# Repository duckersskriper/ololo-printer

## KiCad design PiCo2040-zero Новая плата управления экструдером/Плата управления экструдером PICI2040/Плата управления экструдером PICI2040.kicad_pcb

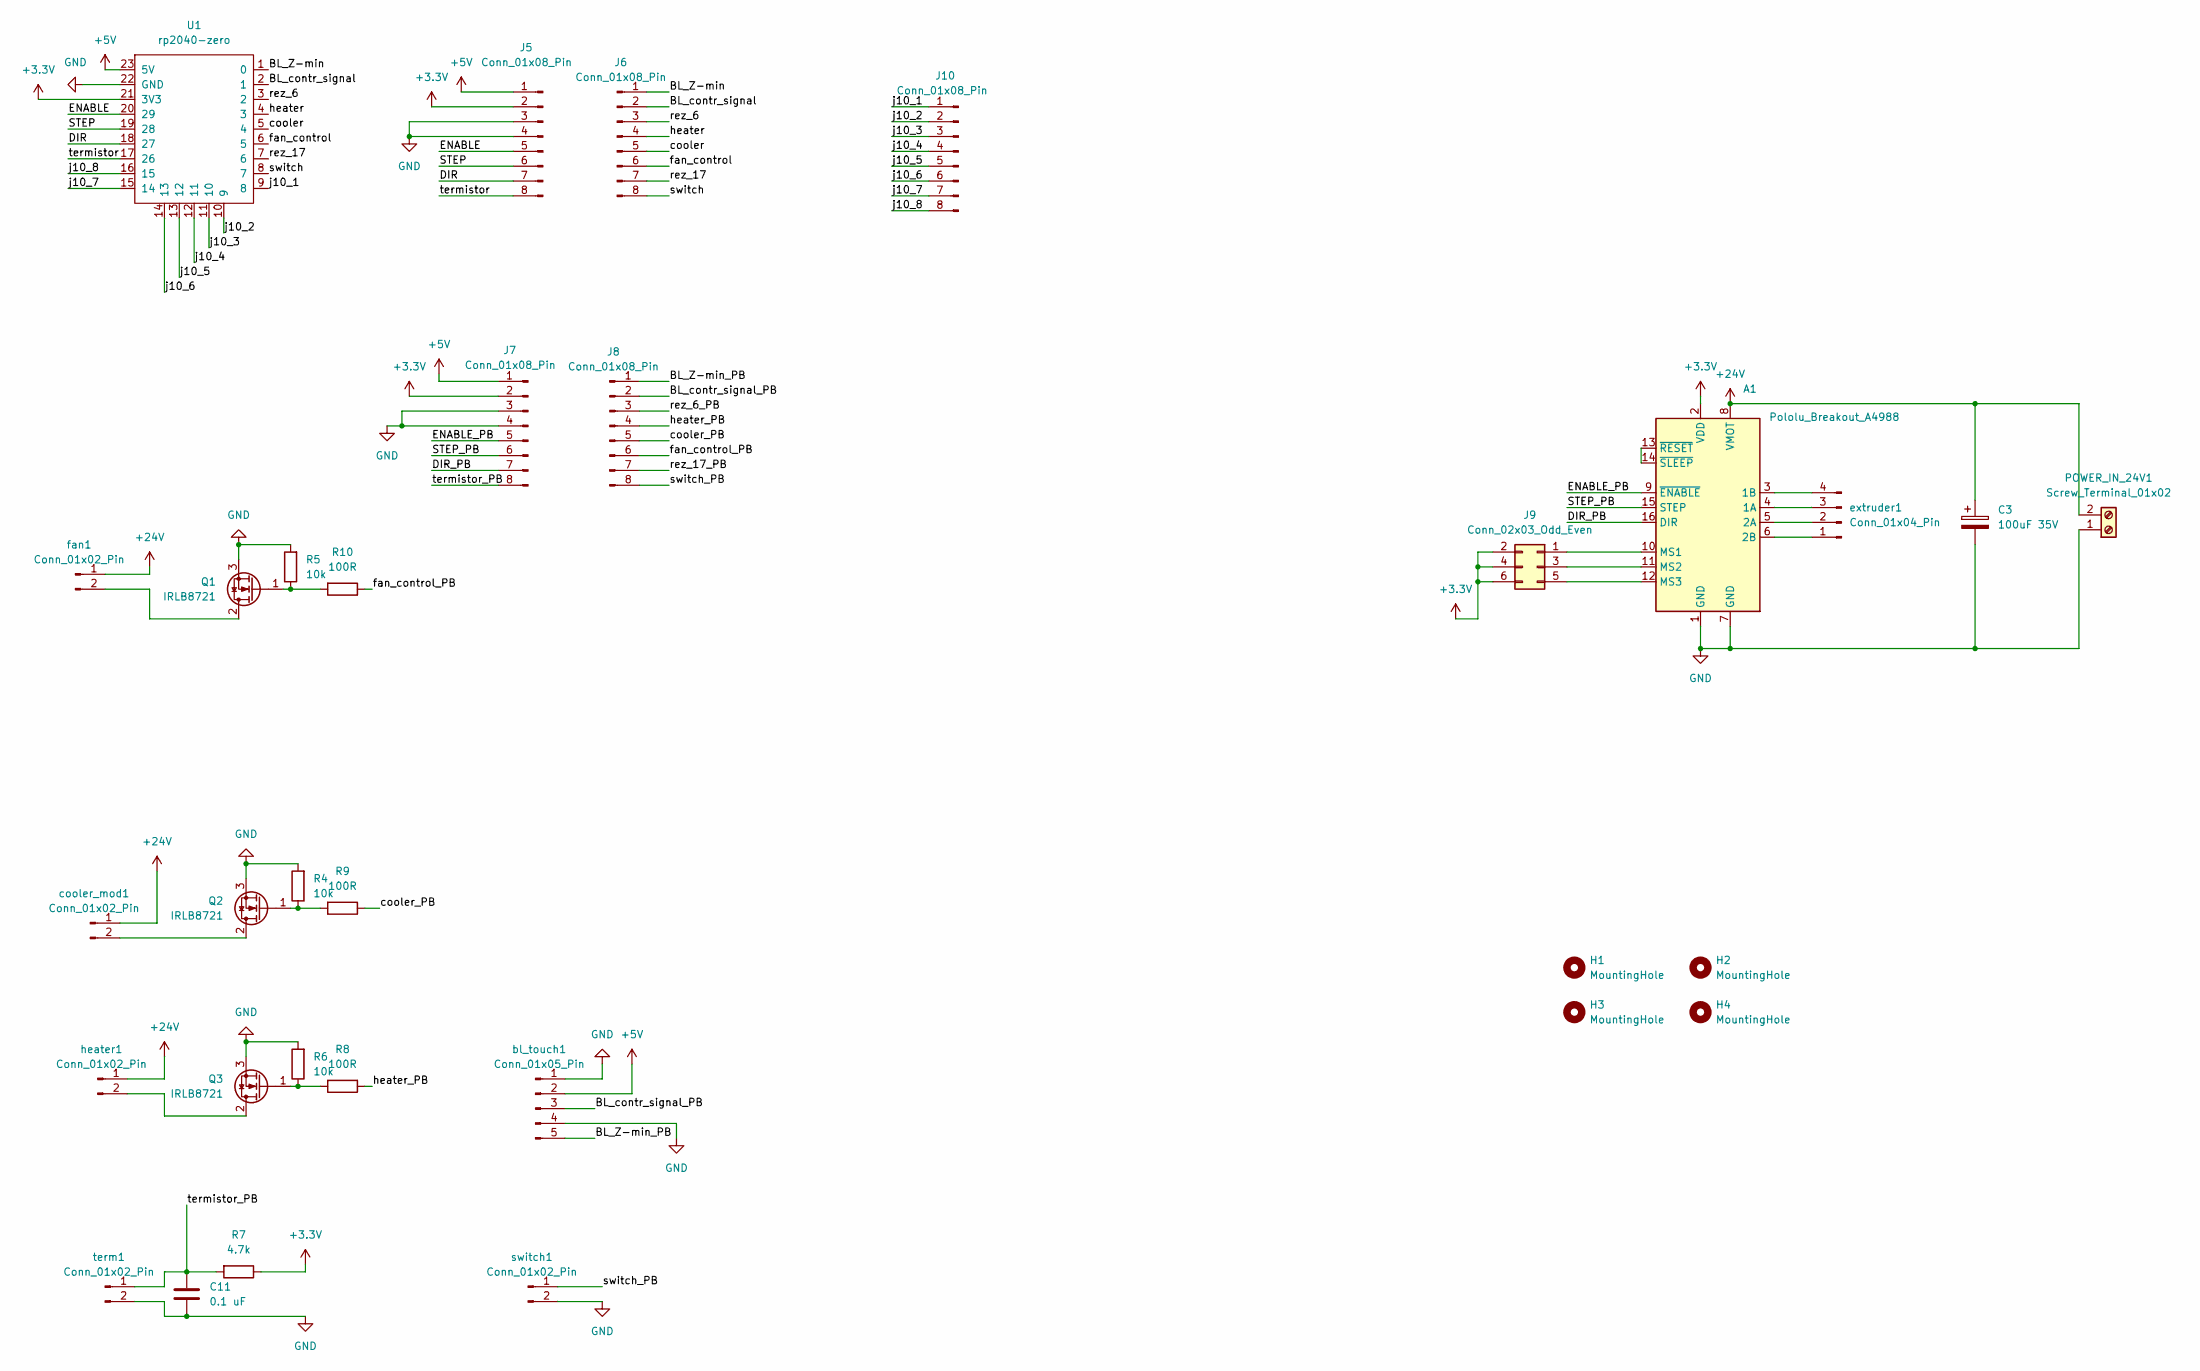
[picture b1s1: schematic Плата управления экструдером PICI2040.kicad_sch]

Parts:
A1: Pololu_Breakout_A4988; Pololu_Breakout-16_15.2x20.3mm
C3: 100uF 35V; CP_Radial_D6.3mm_P2.50mm
C11: 0.1 uF; C_0805_2012Metric_Pad1.18x1.45mm_HandSolder
H1, H2, H3, H4: MountingHole; MountingHole_3.2mm_M3
J5, J6, J10: Conn_01x08_Pin; PinSocket_1x08_P2.54mm_Vertical
J7, J8: Conn_01x08_Pin; PinHeader_1x08_P2.54mm_Vertical
J9: Conn_02x03_Odd_Even; PinHeader_2x03_P2.54mm_Vertical
POWER_IN_24V1: Screw_Terminal_01x02; TerminalBlock_Phoenix_PT-1,5-2-5.0-H_1x02_P5.00mm_Horizontal
Q1, Q2, Q3: IRLB8721; TO-220-3_Vertical
R4, R5, R6: 10k; R_0805_2012Metric_Pad1.20x1.40mm_HandSolder
R7: 4.7k; R_0805_2012Metric_Pad1.20x1.40mm_HandSolder
R8, R9, R10: 100R; R_0805_2012Metric_Pad1.20x1.40mm_HandSolder
U1: rp2040-zero; rp2040-zero-smd
bl_touch1: Conn_01x05_Pin; JST_XH_B5B-XH-A_1x05_P2.50mm_Vertical
cooler_mod1: Conn_01x02_Pin; JST_XH_B2B-XH-A_1x02_P2.50mm_Vertical
extruder1: Conn_01x04_Pin; JST_XH_B4B-XH-A_1x04_P2.50mm_Vertical
fan1: Conn_01x02_Pin; JST_XH_B2B-XH-A_1x02_P2.50mm_Vertical
heater1: Conn_01x02_Pin; JST_XH_B2B-XH-A_1x02_P2.50mm_Vertical
switch1: Conn_01x02_Pin; JST_XH_B2B-XH-A_1x02_P2.50mm_Vertical
term1: Conn_01x02_Pin; JST_XH_B2B-XH-A_1x02_P2.50mm_Vertical

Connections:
+3.3V: A1.2 (VDD), J5.2, J7.2, J9.2, J9.4, J9.6, R7.1, U1.21 (3V3)
+5V: J5.1, J7.1, U1.23 (5V), bl_touch1.2
+24V: A1.8 (VMOT), C3.1, POWER_IN_24V1.2, cooler_mod1.1, fan1.1, heater1.1
/BL_Z-min: J6.1, U1.1 (0)
/BL_Z-min_PB: J8.1, bl_touch1.5
/BL_contr_signal: J6.2, U1.2 (1)
/BL_contr_signal_PB: J8.2, bl_touch1.3
/DIR: J5.7, U1.18 (27)
/DIR_PB: A1.16 (DIR), J7.7
/ENABLE: J5.5, U1.20 (29)
/ENABLE_PB: A1.9 (~ENABLE), J7.5
/STEP: J5.6, U1.19 (28)
/STEP_PB: A1.15 (STEP), J7.6
/cooler: J6.5, U1.5 (4)
/cooler_PB: J8.5, R9.1
/fan_control: J6.6, U1.6 (5)
/fan_control_PB: J8.6, R10.1
/heater: J6.4, U1.4 (3)
/heater_PB: J8.4, R8.1
/j10_1: J10.1, U1.9 (8)
/j10_2: J10.2, U1.10 (9)
/j10_3: J10.3, U1.11 (10)
/j10_4: J10.4, U1.12 (11)
/j10_5: J10.5, U1.13 (12)
/j10_6: J10.6, U1.14 (13)
/j10_7: J10.7, U1.15 (14)
/j10_8: J10.8, U1.16 (15)
/rez_6: J6.3, U1.3 (2)
/rez_6_PB: J8.3
/rez_17: J6.7, U1.7 (6)
/rez_17_PB: J8.7
/switch: J6.8, U1.8 (7)
/switch_PB: J8.8, switch1.1
/termistor: J5.8, U1.17 (26)
/termistor_PB: C11.1, J7.8, R7.2, term1.1
GND: A1.1 (GND), A1.7 (GND), C3.2, C11.2, J5.3, J5.4, J7.3, J7.4, POWER_IN_24V1.1, Q1.3 (S), Q2.3 (S), Q3.3 (S), R4.2, R5.2, R6.2, U1.22 (GND), bl_touch1.1, bl_touch1.4, switch1.2, term1.2
unnamed: A1.4 (1A), extruder1.3
unnamed: A1.3 (1B), extruder1.4
unnamed: A1.5 (2A), extruder1.2
unnamed: A1.6 (2B), extruder1.1
unnamed: A1.10 (MS1), J9.1
unnamed: A1.11 (MS2), J9.3
unnamed: A1.12 (MS3), J9.5
unnamed: A1.13 (~RESET), A1.14 (~SLEEP)
unnamed: Q1.2 (D), fan1.2
unnamed: Q1.1 (G), R5.1, R10.2
unnamed: Q2.2 (D), cooler_mod1.2
unnamed: Q2.1 (G), R4.1, R9.2
unnamed: Q3.2 (D), heater1.2
unnamed: Q3.1 (G), R6.1, R8.2

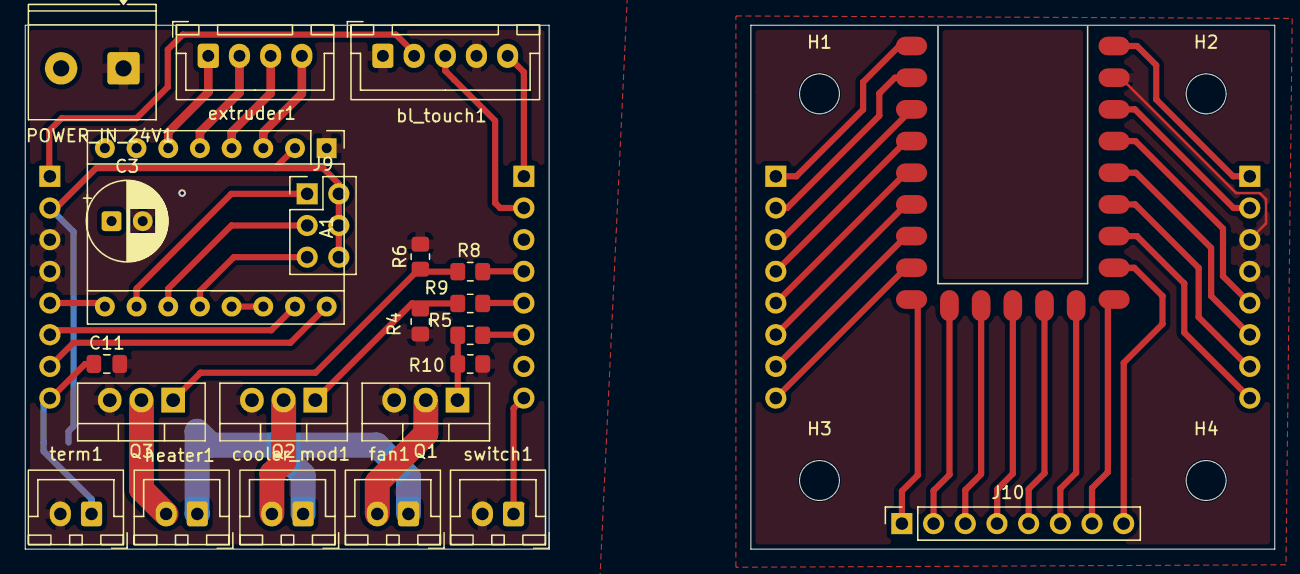
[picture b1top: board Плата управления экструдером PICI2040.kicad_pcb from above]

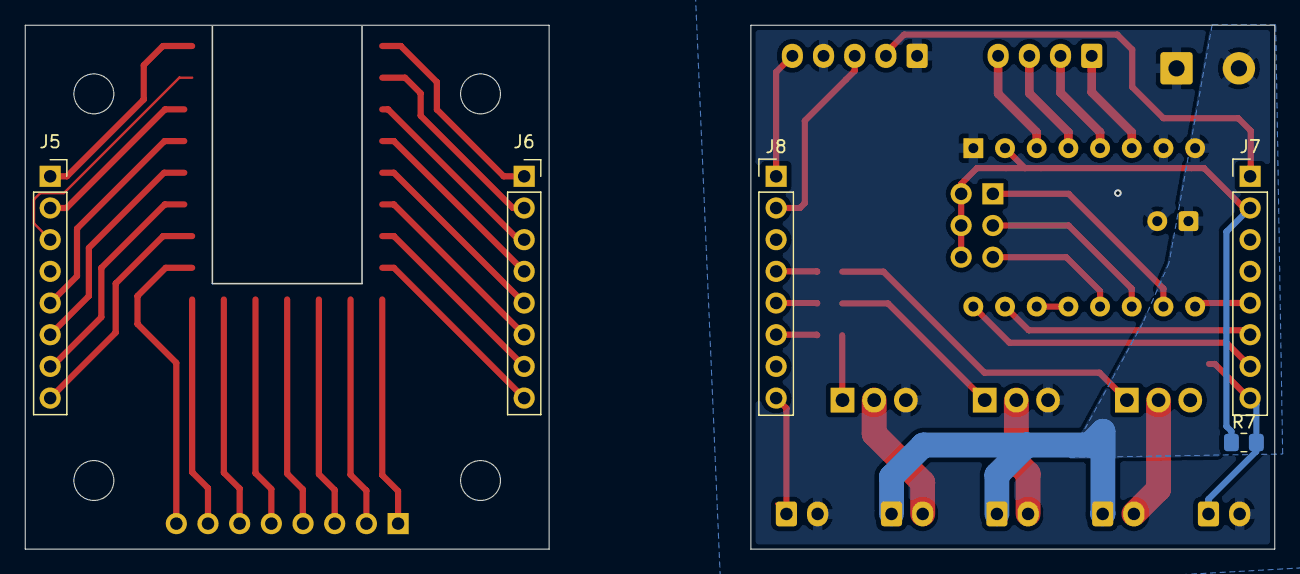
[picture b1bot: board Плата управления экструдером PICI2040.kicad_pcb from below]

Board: 2 copper layers, 42.0 x 42.0 mm, 32 parts (5 on the bottom side), 48 nets.

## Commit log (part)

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2026-01-21 ololo
2026-01-21 first_coomit
2026-01-21 work-at-home
2026-01-22 portal_red
2026-01-22 правка бегунок Х
2026-01-23 Создание печатающей головки
2026-01-26 редактирование печатающей головки
2026-01-27 Печатающая голова
2026-01-28 переделка механики coreXY
2026-01-28 Правка схемы corexy дома
2026-01-29 Правка крепления натяжителя, Бегунка оси У
2026-01-29 Правка крепления натяжителя
2026-01-29 правка углового обвода
2026-01-30 доделки
2026-01-30 Правки печат головы
2026-02-08 Проработка механизма оси Z
2026-02-09 новый детали стола
2026-02-09 Правка направляющих стола
2026-02-10 ololo1
2026-02-11 рамка стола
2026-02-11 Сборка рамы стола
2026-02-12 Добавление стола
2026-02-12 Крепление оси Z
2026-02-13 Правка зазоров натяжителя Z
2026-02-13 Правка структура изделия для профилей(только)
2026-02-17 бегунок по оси х исполнение 01.grb
2026-02-24 ребра жесткости
2026-02-24 electronics
2026-03-03 правки отверстий
2026-03-06 Добавлен микрик
2026-03-10 Концевики
2026-03-26 с рабочего компа
2026-04-17 Новая сборка
2026-04-19 Новая печат головка
2026-04-20 Новая головка и втулки оси x
2026-04-28 Перед началом работ
2026-04-28 Упрощенное сопло
2026-04-29 Держатель обдува
2026-05-08 Новый конфиг
2026-05-28 Новая плата управления экструдера
2026-05-28 Плата управления
2026-05-28 Плата управления_обновл
2026-05-28 разводка платы
2026-05-29 Плата управления раздел
2026-05-31 Коннекторы
2026-06-01 Правка платы
2026-06-02 Начало трассировки
2026-06-02 Трассировка вечером
2026-06-03 Трассировка USB type C
2026-06-03 Изменение под PR2040-zero
2026-06-05 Трассировка
2026-06-09 Мелкие правки платы
2026-06-24 Гравер
2026-06-25 Механика гравера
2026-06-30 Новое крепление 3
2026-06-30 Правка крепления оси Х
